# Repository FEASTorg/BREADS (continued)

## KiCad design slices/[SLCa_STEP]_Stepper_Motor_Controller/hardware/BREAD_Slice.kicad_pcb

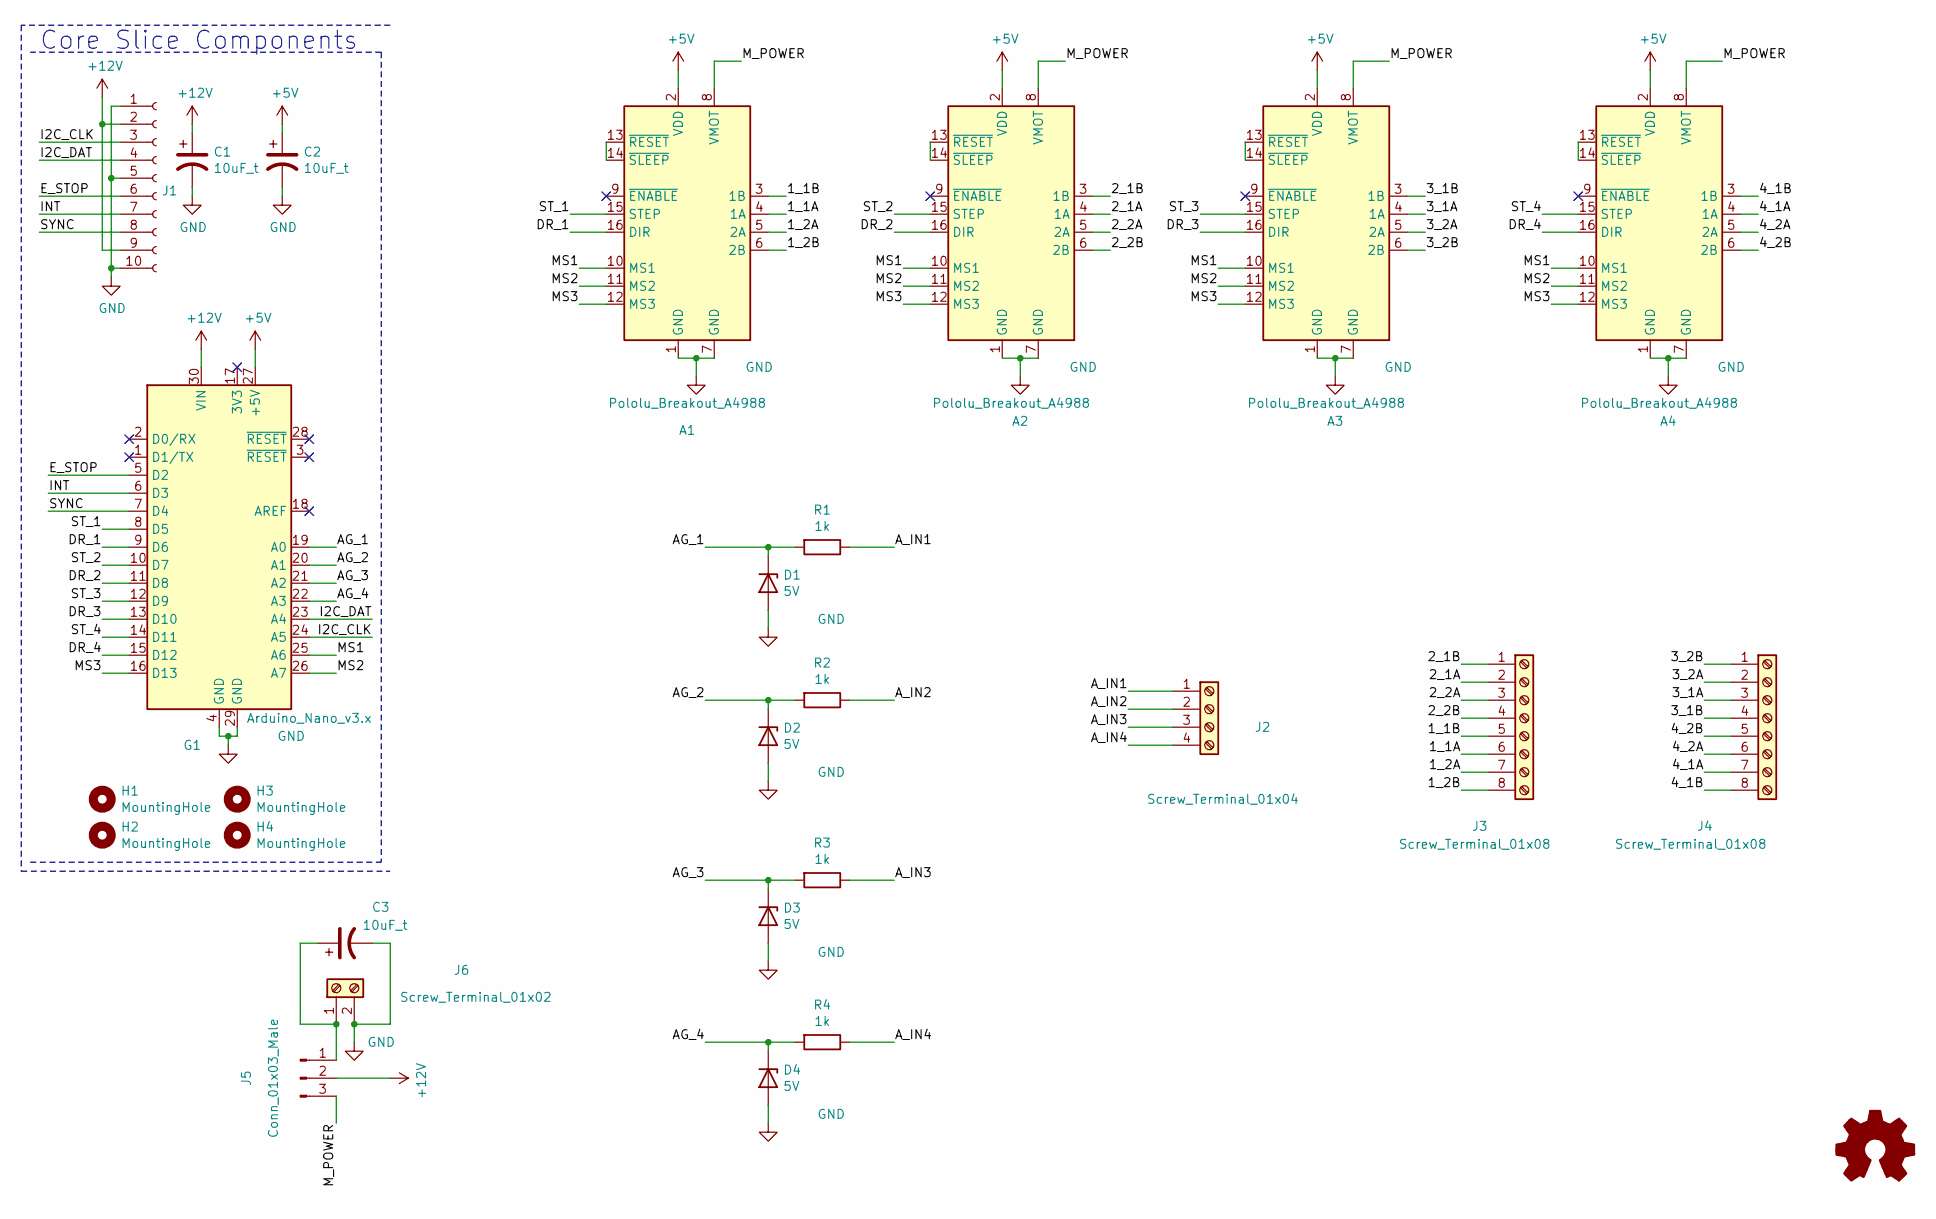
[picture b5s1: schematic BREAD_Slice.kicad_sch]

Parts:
A1, A2, A3, A4: Pololu_Breakout_A4988; Pololu_Breakout-16_15.2x20.3mm
C1, C2, C3: 10uF_t; C_2312; Part # T491C106K025AT
D1, D2, D3, D4: 5V; D_1206_3216Metric_Pad1.42x1.75mm_HandSolder
G1: Arduino_Nano_v3.x; Arduino_Nano
H1, H2, H3, H4: MountingHole; MountingHole_3.2mm_M3_DIN965_Pad
J1: Conn_01x10_Female; PinSocket_1x10_P2.54mm_Horizontal
J2: Screw_Terminal_01x04; TerminalBlock_TE_282834-4_1x04_P2.54mm_Horizontal
J3, J4: Screw_Terminal_01x08; TerminalBlock_TE_282834-8_1x08_P2.54mm_Horizontal
J5: Conn_01x03_Male; PinSocket_1x03_P2.54mm_Vertical
J6: Screw_Terminal_01x02; TerminalBlock_TE_282834-2_1x02_P2.54mm_Horizontal
Logo1: Logo_Open_Hardware_Small; OSHW-Symbol_6.7x6mm_SilkScreen
R1, R2, R3, R4: 1k; R_1206_3216Metric_Pad1.30x1.75mm_HandSolder

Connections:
+5V: A1.2 (VDD), A2.2 (VDD), A3.2 (VDD), A4.2 (VDD), C2.1, G1.27 (+5V)
+12V: C1.1, G1.30 (VIN), J1.2, J1.9, J5.2
/1_1A: A1.4 (1A), J3.6
/1_1B: A1.3 (1B), J3.5
/1_2A: A1.5 (2A), J3.7
/1_2B: A1.6 (2B), J3.8
/2_1A: A2.4 (1A), J3.2
/2_1B: A2.3 (1B), J3.1
/2_2A: A2.5 (2A), J3.3
/2_2B: A2.6 (2B), J3.4
/3_1A: A3.4 (1A), J4.3
/3_1B: A3.3 (1B), J4.4
/3_2A: A3.5 (2A), J4.2
/3_2B: A3.6 (2B), J4.1
/4_1A: A4.4 (1A), J4.7
/4_1B: A4.3 (1B), J4.8
/4_2A: A4.5 (2A), J4.6
/4_2B: A4.6 (2B), J4.5
/AG_1: D1.1 (K), G1.19 (A0), R1.2
/AG_2: D2.1 (K), G1.20 (A1), R2.2
/AG_3: D3.1 (K), G1.21 (A2), R3.2
/AG_4: D4.1 (K), G1.22 (A3), R4.2
/A_IN1: J2.1, R1.1
/A_IN2: J2.2, R2.1
/A_IN3: J2.3, R3.1
/A_IN4: J2.4, R4.1
/DR_1: A1.16 (DIR), G1.9 (D6)
/DR_2: A2.16 (DIR), G1.11 (D8)
/DR_3: A3.16 (DIR), G1.13 (D10)
/DR_4: A4.16 (DIR), G1.15 (D12)
/E_STOP: G1.5 (D2), J1.6
/I2C_CLK: G1.24 (A5), J1.3
/I2C_DAT: G1.23 (A4), J1.4
/INT: G1.6 (D3), J1.7
/MS1: A1.10 (MS1), A2.10 (MS1), A3.10 (MS1), A4.10 (MS1), G1.25 (A6)
/MS2: A1.11 (MS2), A2.11 (MS2), A3.11 (MS2), A4.11 (MS2), G1.26 (A7)
/MS3: A1.12 (MS3), A2.12 (MS3), A3.12 (MS3), A4.12 (MS3), G1.16 (D13)
/M_POWER: A1.8 (VMOT), A2.8 (VMOT), A3.8 (VMOT), A4.8 (VMOT), J5.3
/ST_1: A1.15 (STEP), G1.8 (D5)
/ST_2: A2.15 (STEP), G1.10 (D7)
/ST_3: A3.15 (STEP), G1.12 (D9)
/ST_4: A4.15 (STEP), G1.14 (D11)
/SYNC: G1.7 (D4), J1.8
GND: A1.1 (GND), A1.7 (GND), A2.1 (GND), A2.7 (GND), A3.1 (GND), A3.7 (GND), A4.1 (GND), A4.7 (GND), C1.2, C2.2, C3.2, D1.2 (A), D2.2 (A), D3.2 (A), D4.2 (A), G1.4 (GND), G1.29 (GND), J1.1, J1.5, J1.10, J6.2
unnamed: A1.13 (~RESET), A1.14 (~SLEEP)
unnamed: A2.13 (~RESET), A2.14 (~SLEEP)
unnamed: A3.13 (~RESET), A3.14 (~SLEEP)
unnamed: A4.13 (~RESET), A4.14 (~SLEEP)
unnamed: C3.1, J5.1, J6.1

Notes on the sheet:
Core Slice Components

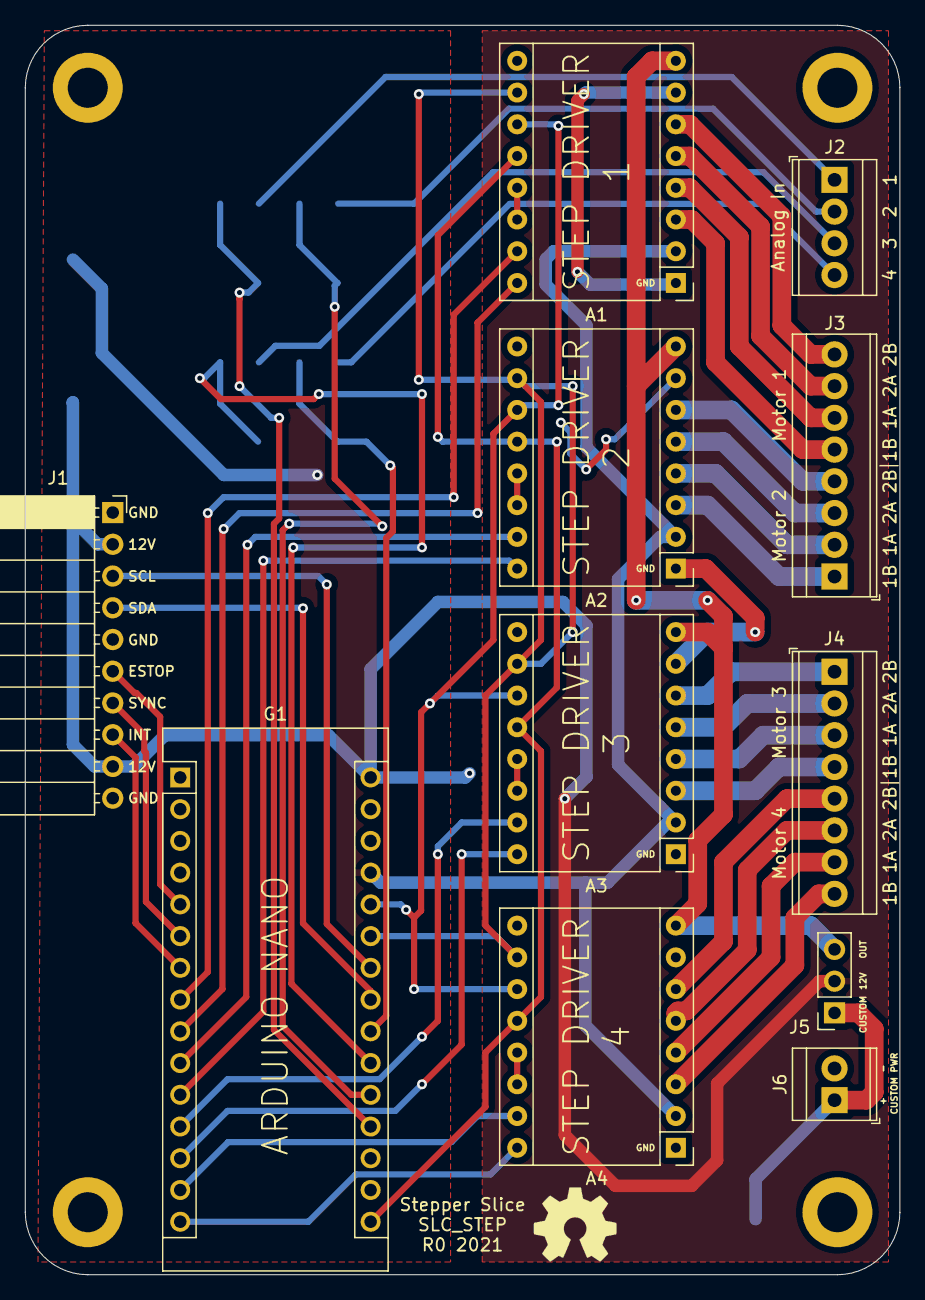
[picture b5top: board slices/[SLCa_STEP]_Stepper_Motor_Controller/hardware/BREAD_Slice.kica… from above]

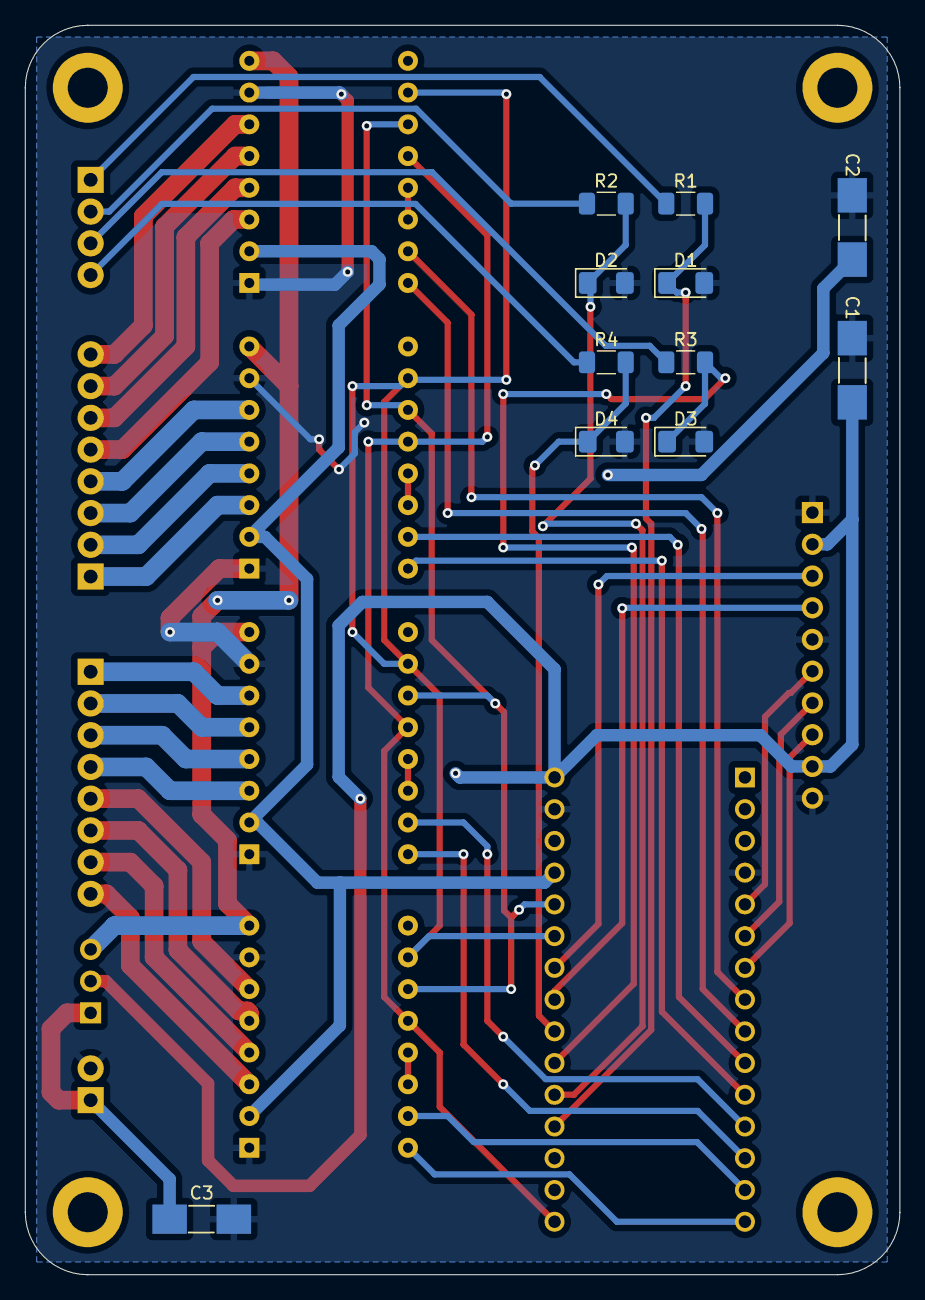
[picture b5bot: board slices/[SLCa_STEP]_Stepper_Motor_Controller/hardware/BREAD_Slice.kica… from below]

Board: 2 copper layers, 70.0 x 100.0 mm, 27 parts (11 on the bottom side), 49 nets.

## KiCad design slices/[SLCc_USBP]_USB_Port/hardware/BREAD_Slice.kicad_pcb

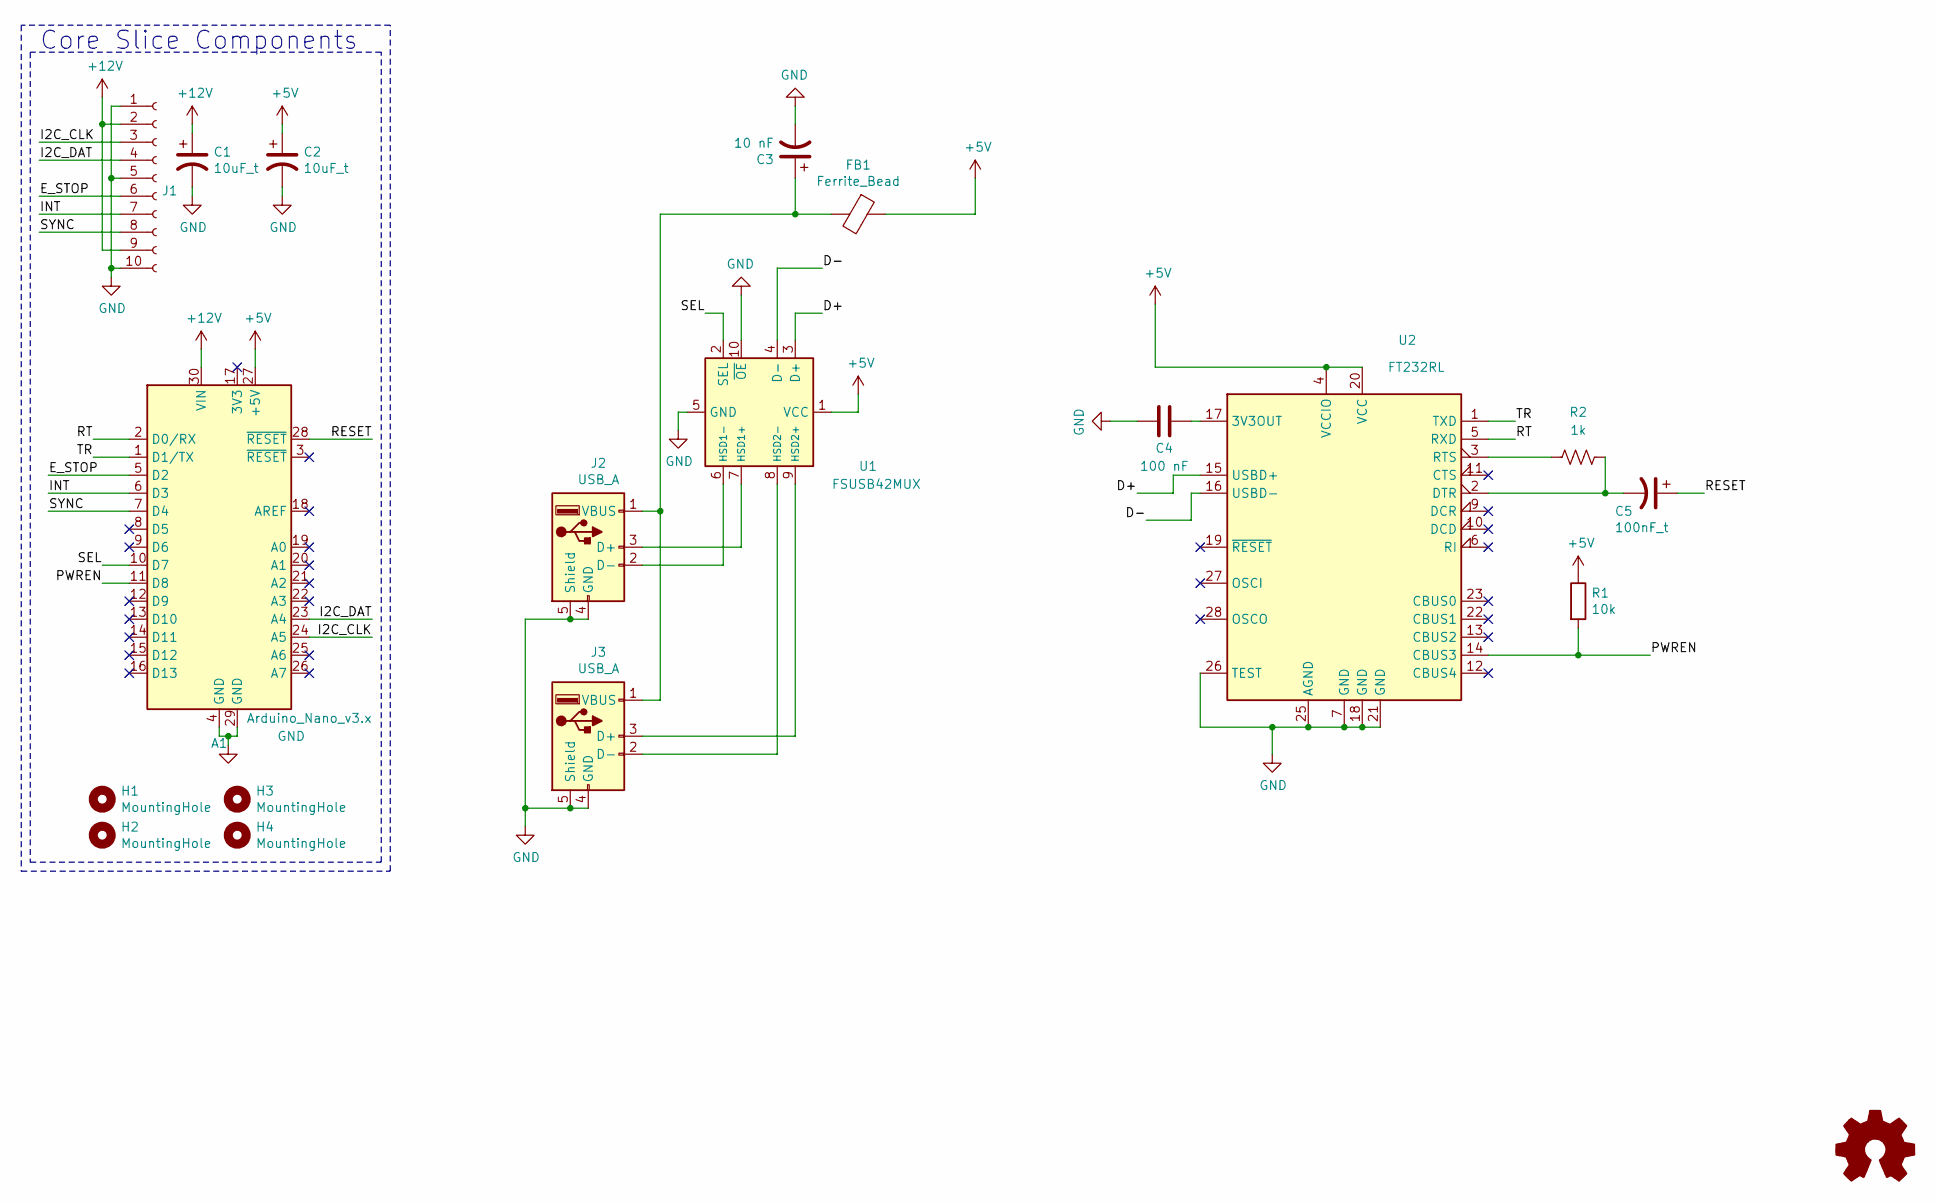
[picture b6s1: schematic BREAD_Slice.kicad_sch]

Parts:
A1: Arduino_Nano_v3.x; Arduino_Nano
C1, C2: 10uF_t; C_2312; Part # T491C106K025AT
C3: 10 nF; C_2312; Part # T491C106K025AT
C4: 100 nF; C_1206_3216Metric_Pad1.33x1.80mm_HandSolder
C5: 100nF_t; C_1206_3216Metric_Pad1.33x1.80mm_HandSolder; Part # T491C106K025AT
FB1: Ferrite_Bead; R_1206_HandSoldering
H1, H2, H3, H4: MountingHole; MountingHole_3.2mm_M3_DIN965_Pad
J1: Conn_01x10_Female; PinSocket_1x10_P2.54mm_Horizontal
J2, J3: USB_A; USB_A_Molex_67643_Horizontal
Logo1: Logo_Open_Hardware_Small; OSHW-Symbol_6.7x6mm_SilkScreen
R1: 10k; R_1206_HandSoldering
R2: 1k; R_1206_3216Metric_Pad1.30x1.75mm_HandSolder
U1: FSUSB42MUX; MSOP-10_3x3mm_P0.5mm
U2: FT232RL; SSOP-28_5.3x10.2mm_P0.65mm

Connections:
+5V: A1.27 (+5V), C2.1, FB1.1, R1.1, U1.1 (VCC), U2.4 (VCCIO), U2.20 (VCC)
+12V: A1.30 (VIN), C1.1, J1.2, J1.9
/D+: U1.3 (D+), U2.15 (USBD+)
/D-: U1.4 (D-), U2.16 (USBD-)
/E_STOP: A1.5 (D2), J1.6
/I2C_CLK: A1.24 (A5), J1.3
/I2C_DAT: A1.23 (A4), J1.4
/INT: A1.6 (D3), J1.7
/PWREN: A1.11 (D8), R1.2, U2.14 (CBUS3)
/RESET: A1.28 (~RESET), C5.1
/RT: A1.2 (D0/RX), U2.5 (RXD)
/SEL: A1.10 (D7), U1.2 (SEL)
/SYNC: A1.7 (D4), J1.8
/TR: A1.1 (D1/TX), U2.1 (TXD)
GND: A1.4 (GND), A1.29 (GND), C1.2, C2.2, C3.2, C4.1, J1.1, J1.5, J1.10, J2.4 (GND), J2.5 (Shield), J3.4 (GND), J3.5 (Shield), U1.5 (GND), U1.10 (~OE), U2.7 (GND), U2.18 (GND), U2.21 (GND), U2.25 (AGND), U2.26 (TEST)
unnamed: C3.1, FB1.2, J2.1 (VBUS), J3.1 (VBUS)
unnamed: C4.2, U2.17 (3V3OUT)
unnamed: J2.2 (D-), U1.6 (HSD1-)
unnamed: J2.3 (D+), U1.7 (HSD1+)
unnamed: J3.2 (D-), U1.8 (HSD2-)
unnamed: J3.3 (D+), U1.9 (HSD2+)
unnamed: C5.2, R2.2, U2.2 (DTR)
unnamed: R2.1, U2.3 (RTS)

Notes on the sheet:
Core Slice Components

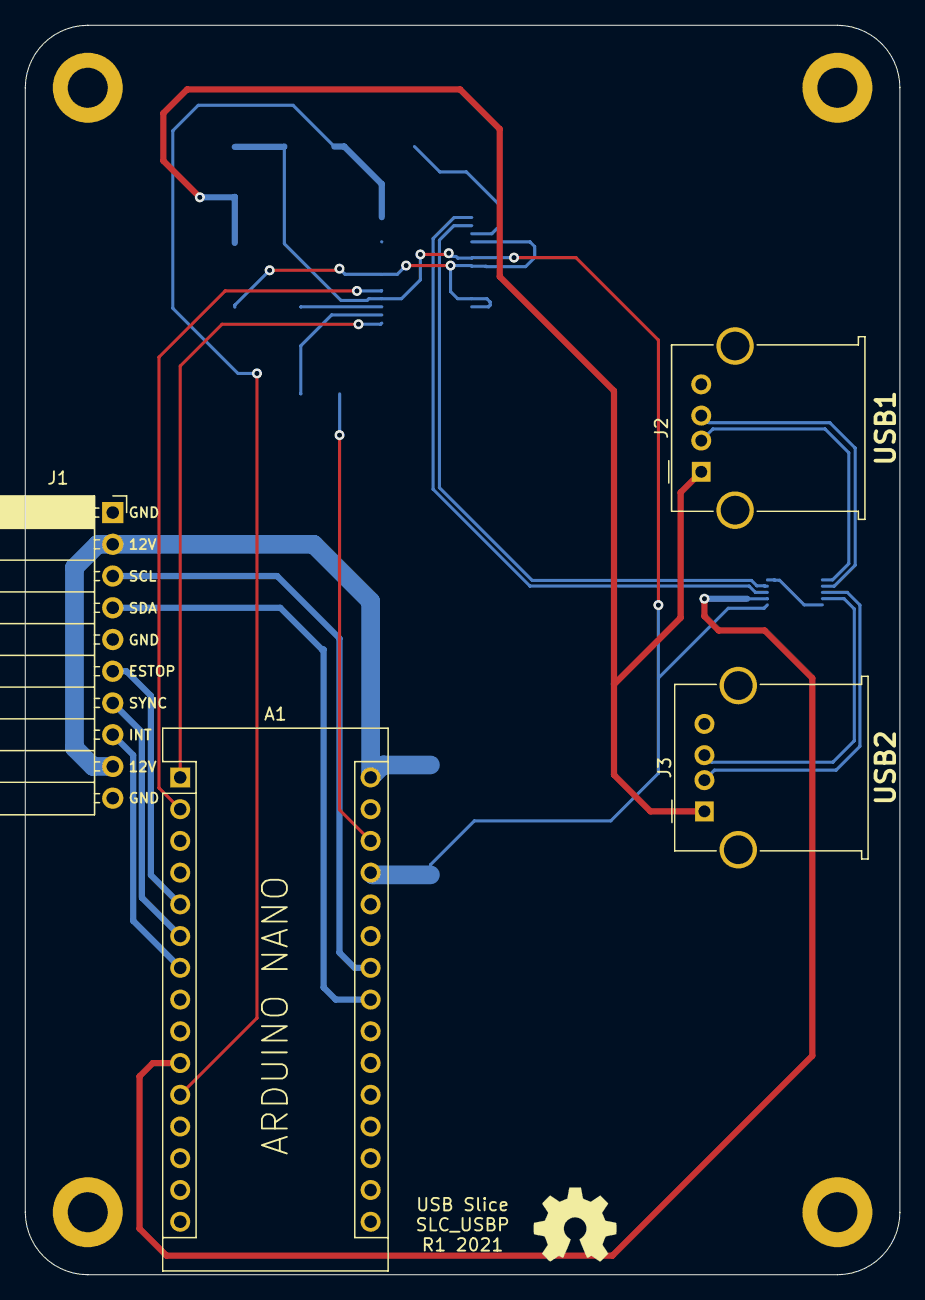
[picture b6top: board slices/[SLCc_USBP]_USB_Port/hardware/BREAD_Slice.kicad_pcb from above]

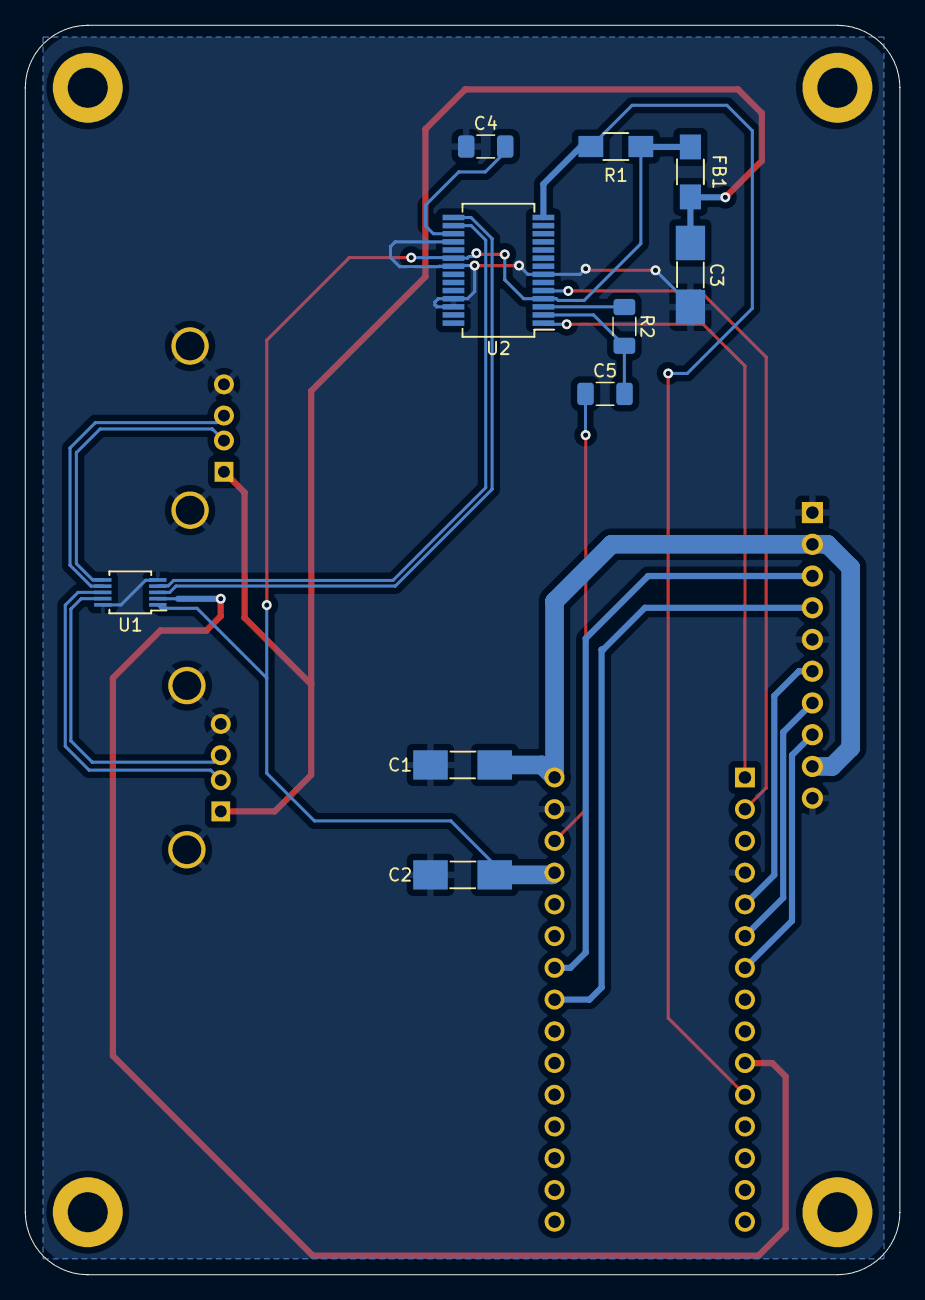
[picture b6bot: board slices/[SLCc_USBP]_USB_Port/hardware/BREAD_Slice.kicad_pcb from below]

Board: 2 copper layers, 70.0 x 100.0 mm, 19 parts (10 on the bottom side), 23 nets.

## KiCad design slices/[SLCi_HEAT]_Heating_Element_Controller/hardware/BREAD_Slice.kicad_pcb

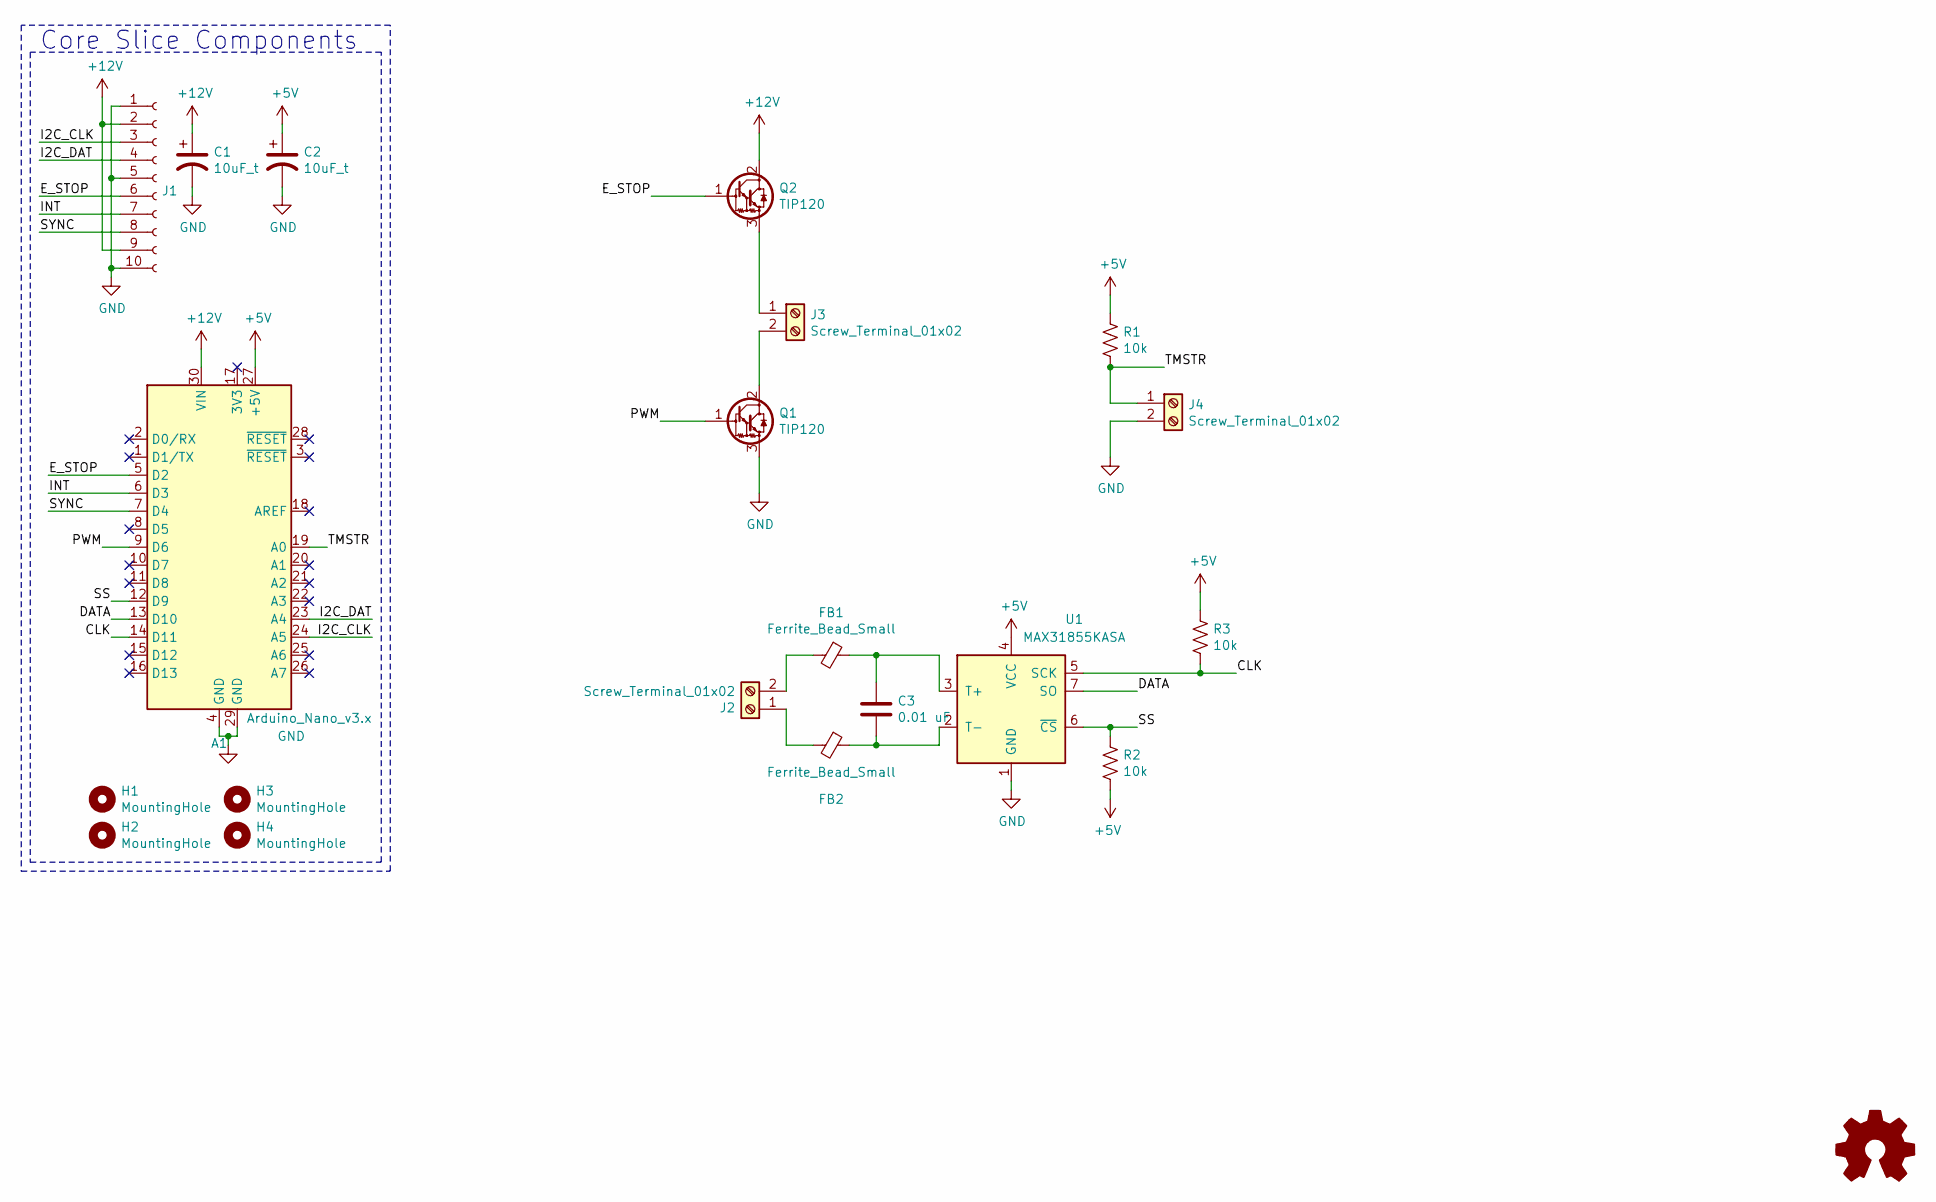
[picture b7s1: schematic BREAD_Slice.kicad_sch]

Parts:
A1: Arduino_Nano_v3.x; Arduino_Nano
C1, C2: 10uF_t; C_2312; Part # T491C106K025AT
C3: 0.01 uF; C_1206_HandSoldering
FB1, FB2: Ferrite_Bead_Small; R_1206_HandSoldering
H1, H2, H3, H4: MountingHole; MountingHole_3.2mm_M3_DIN965_Pad
J1: Conn_01x10_Female; PinSocket_1x10_P2.54mm_Horizontal
J2, J3, J4: Screw_Terminal_01x02; TerminalBlock_Pheonix_MKDS1.5-2pol
Logo1: Logo_Open_Hardware_Small; OSHW-Symbol_6.7x6mm_SilkScreen
Q1, Q2: TIP120; TO-220-3_Vertical
R1, R2, R3: 10k; R_1206_HandSoldering
U1: MAX31855KASA; SOIC-8_3.9x4.9mm_P1.27mm

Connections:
+5V: A1.27 (+5V), C2.1, R1.1, R2.2, R3.1, U1.4 (VCC)
+12V: A1.30 (VIN), C1.1, J1.2, J1.9, Q2.2 (C)
/CLK: A1.14 (D11), R3.2, U1.5 (SCK)
/DATA: A1.13 (D10), U1.7 (SO)
/E_STOP: A1.5 (D2), J1.6, Q2.1 (B)
/I2C_CLK: A1.24 (A5), J1.3
/I2C_DAT: A1.23 (A4), J1.4
/INT: A1.6 (D3), J1.7
/PWM: A1.9 (D6), Q1.1 (B)
/SS: A1.12 (D9), R2.1, U1.6 (~CS)
/SYNC: A1.7 (D4), J1.8
/TMSTR: A1.19 (A0), J4.1, R1.2
GND: A1.4 (GND), A1.29 (GND), C1.2, C2.2, J1.1, J1.5, J1.10, J4.2, Q1.3 (E), U1.1 (GND)
unnamed: C3.1, FB1.1, U1.3 (T+)
unnamed: C3.2, FB2.1, U1.2 (T-)
unnamed: FB1.2, J2.2
unnamed: FB2.2, J2.1
unnamed: J3.1, Q2.3 (E)
unnamed: J3.2, Q1.2 (C)

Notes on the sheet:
Core Slice Components

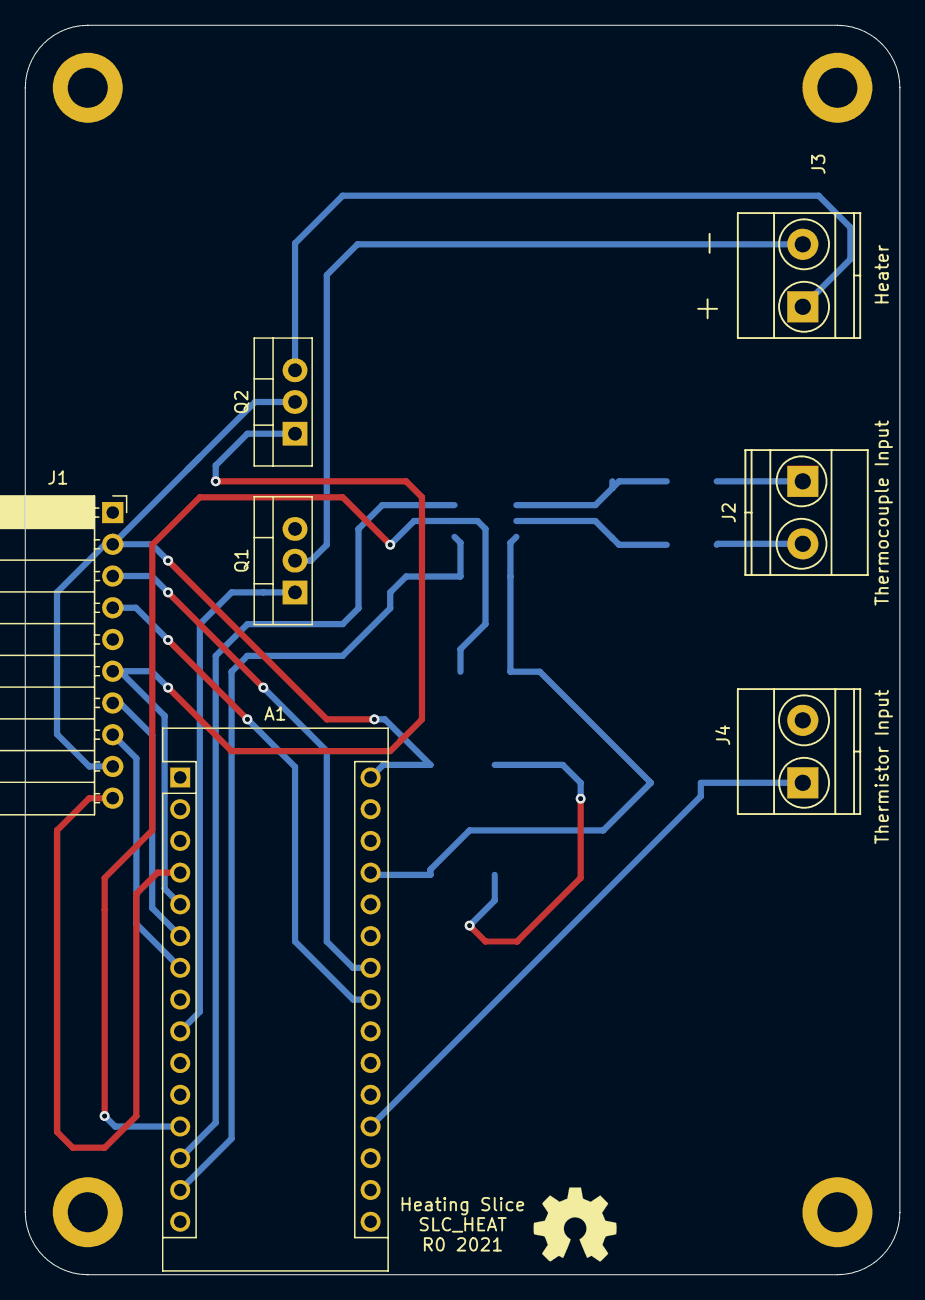
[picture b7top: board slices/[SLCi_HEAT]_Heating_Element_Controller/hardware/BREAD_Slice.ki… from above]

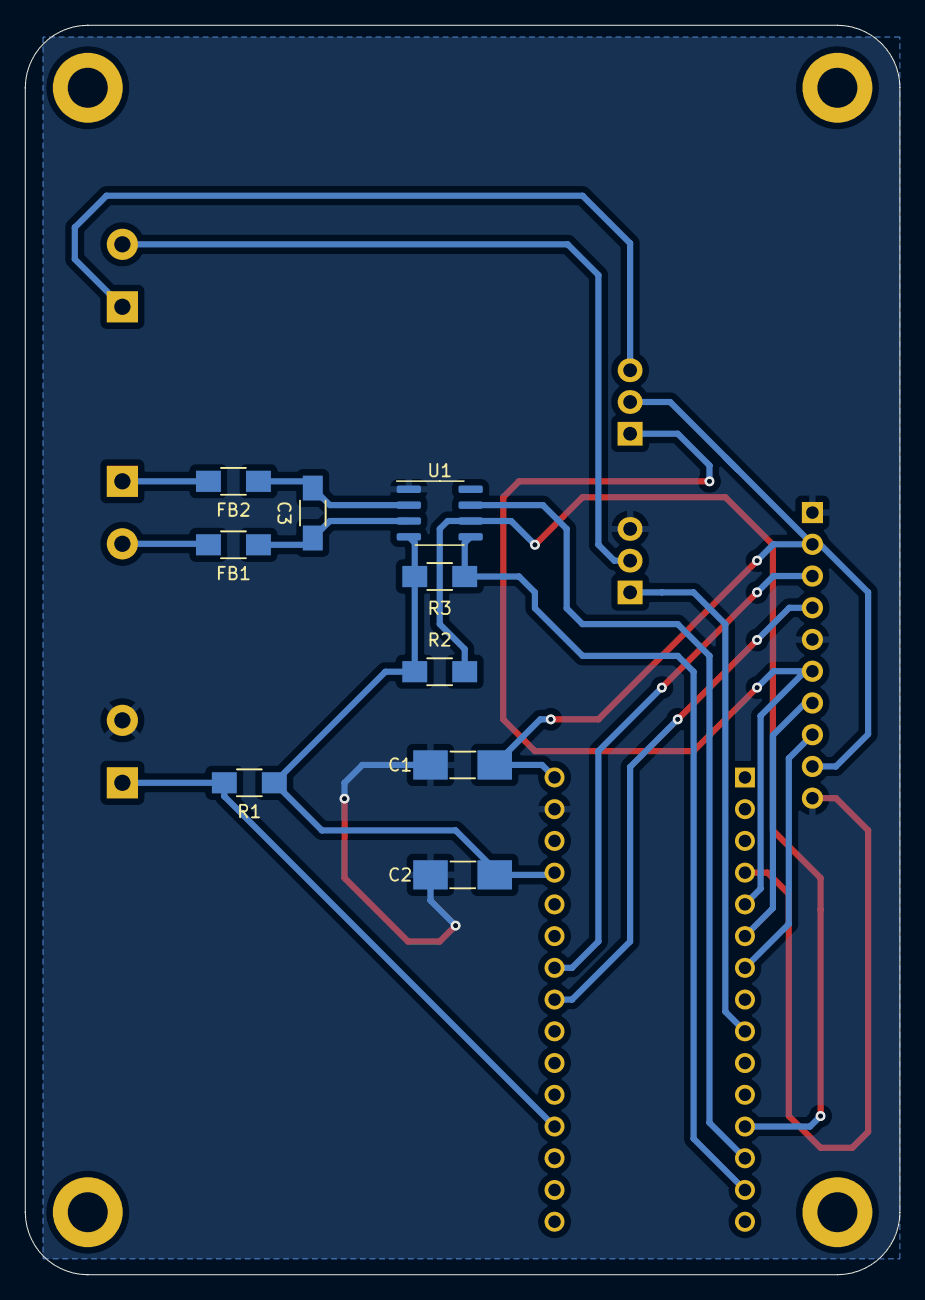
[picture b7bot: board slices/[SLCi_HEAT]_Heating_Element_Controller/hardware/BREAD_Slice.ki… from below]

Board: 2 copper layers, 70.0 x 100.0 mm, 21 parts (9 on the bottom side), 19 nets.

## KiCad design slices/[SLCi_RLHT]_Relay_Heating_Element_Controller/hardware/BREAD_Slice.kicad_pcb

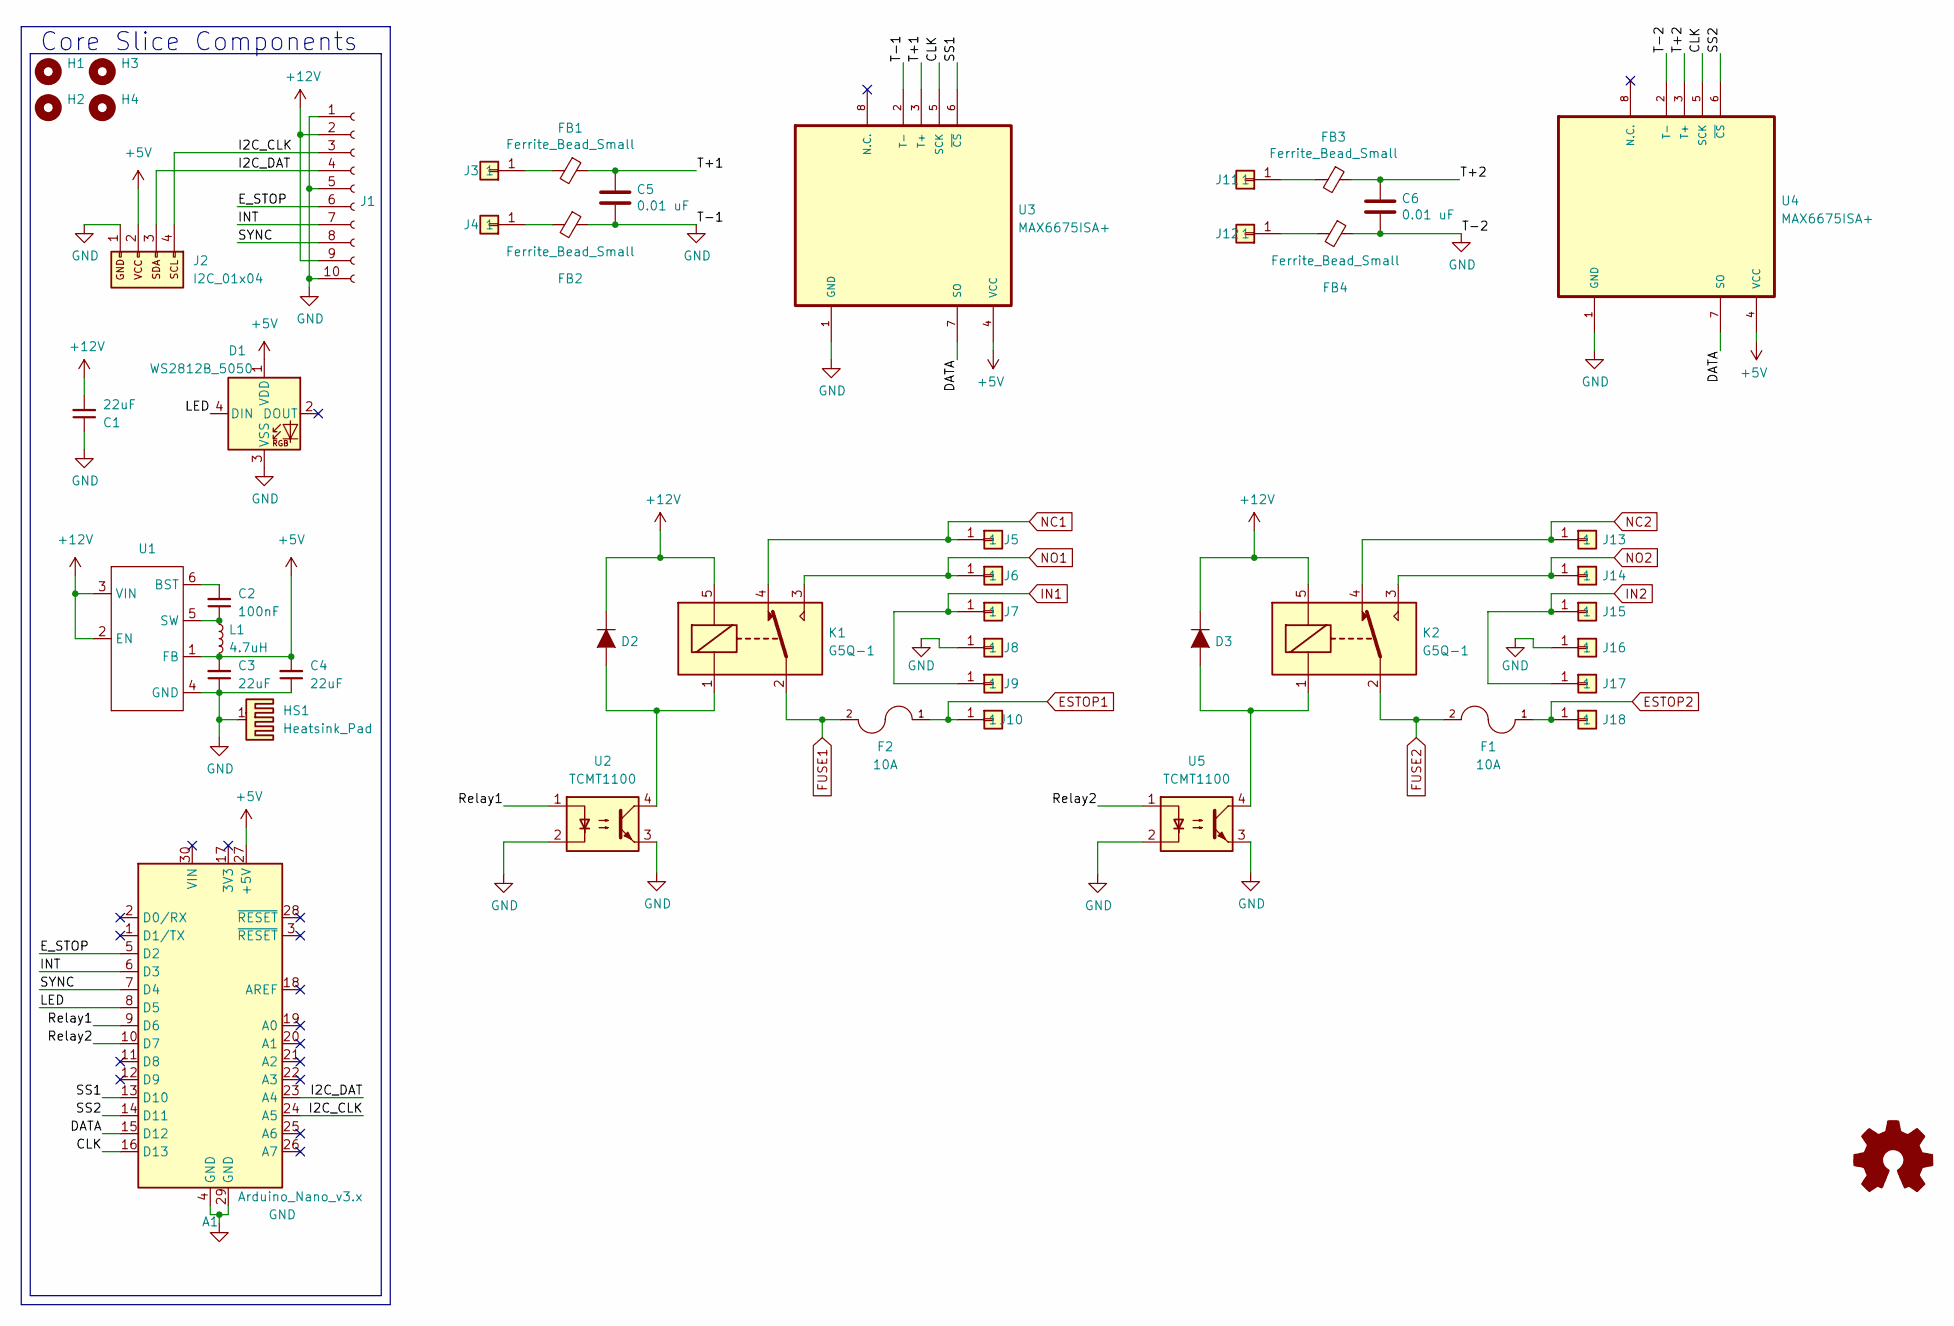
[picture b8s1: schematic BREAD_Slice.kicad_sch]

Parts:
A1: Arduino_Nano_v3.x; Arduino_Nano
C1, C3, C4: 22uF; C_1206_3216Metric
C2: 100nF; C_1206_3216Metric
C5, C6: 0.01 uF; C_1206_3216Metric
D1: WS2812B_5050; WS2812-5050-4PIN
D2, D3: General_Purpose_Diode; D_DO-35_SOD27_P7.62mm_Horizontal; Part # 1N914BWS
F1, F2: 10A; Glass Fuse Clip 5x20MM; Part # 3522-2
FB1, FB2, FB3, FB4: Ferrite_Bead_Small; R_1206_3216Metric
H1, H2, H3, H4: MountingHole; MountingHole_5mm
HS1: Heatsink_Pad; Thermal Pad
J1: Conn_01x10_Female; PinSocket_1x10_P2.54mm_Horizontal
J2: I2C_01x04; JST_SH_SM04B-SRSS-TB_1x04-1MP_P1.00mm_Horizontal
J3, J11, J12: Term_PressFit_Phoenix_Contact; Term_PressFit_3.5mm_H_PC
J4: Term_PressFit_Phoenix_Contact; Term_PressFit_3.5mm_H_ENDCAP_PC
J5: Term_PressFit_Phoenix_Contact; Term_PressFit_5mm_H_ENDCAP_PC_HVRELAY
J6, J7, J8, J9, J10, J13, J14, J15, J16, J17, J18: Term_PressFit_Phoenix_Contact; Term_PressFit_5mm_H_PC_HVRELAY
K1, K2: G5Q-1; Relay_SPDT_Omron-G5Q-1
L1: 4.7uH; L_1210_3225Metric
U1: TSOT-23-6
U2, U5: TCMT1100; SOP-4_4.4x2.6mm_P1.27mm
U3, U4: MAX6675ISA+; SOIC127P600X175-8N

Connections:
+5V: A1.27 (+5V), C3.2, C4.2, D1.1 (VDD), J2.2, L1.2, U1.1 (FB), U3.4 (VCC), U4.4 (VCC)
+12V: C1.2, D2.1 (K), D3.1 (K), J1.2, J1.9, K1.5, K2.5, U1.2 (EN), U1.3 (VIN)
/CLK: A1.16 (D13), U3.5 (SCK), U4.5 (SCK)
/DATA: A1.15 (D12), U3.7 (SO), U4.7 (SO)
/E_STOP: A1.5 (D2), J1.6
/I2C_CLK: A1.24 (A5), J1.3, J2.4
/I2C_DAT: A1.23 (A4), J1.4, J2.3
/INT: A1.6 (D3), J1.7
/LED: A1.8 (D5), D1.4 (DIN)
/Relay1: A1.9 (D6), U2.1
/Relay2: A1.10 (D7), U5.1
/SS1: A1.13 (D10), U3.6 (~CS)
/SS2: A1.14 (D11), U4.6 (~CS)
/SYNC: A1.7 (D4), J1.8
/T+1: C5.1, FB1.1, U3.3 (T+)
/T+2: C6.1, FB3.1, U4.3 (T+)
ESTOP1: F2.1, J10.1
ESTOP2: F1.1, J18.1
FUSE1: F2.2, K1.2
FUSE2: F1.2, K2.2
GND: A1.4 (GND), A1.29 (GND), C1.1, C3.1, C4.1, C5.2, C6.2, D1.3 (VSS), FB2.1, FB4.1, HS1.1, J1.1, J1.5, J1.10, J2.1, J8.1, J16.1, U1.4 (GND), U2.2, U2.3, U3.1 (GND), U3.2 (T-), U4.1 (GND), U4.2 (T-), U5.2, U5.3
IN1: J7.1, J9.1
IN2: J15.1, J17.1
NC1: J5.1, K1.4
NC2: J13.1, K2.4
NO1: J6.1, K1.3
NO2: J14.1, K2.3
unnamed: D2.2 (A), K1.1, U2.4
unnamed: D3.2 (A), K2.1, U5.4
unnamed: FB1.2, J3.1
unnamed: FB2.2, J4.1
unnamed: FB3.2, J11.1
unnamed: FB4.2, J12.1
unnamed: C2.2, U1.6 (BST)
unnamed: C2.1, L1.1, U1.5 (SW)

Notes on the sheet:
Core Slice Components
